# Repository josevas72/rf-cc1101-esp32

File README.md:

# RF CC1101 + ESP32 — placa, firmware ESPHome y caja 3D

Emisor/receptor de radiofrecuencia a **433,92 MHz** con un ESP32 y el módulo **CC1101**
(E07-M1101D), pensado para Home Assistant mediante **ESPHome**. Sirve para controlar por RF
persianas, luces, enchufes o ventiladores con mando, y para escuchar el mando original y mantener
sincronizado el estado.

El repositorio incluye todo lo necesario para reproducirlo: la **placa (PCB)** en KiCad con sus
archivos de fabricación, el **firmware** (plantillas ESPHome) y una **caja imprimible** en 3D.

Hay dos versiones:

- **v2 (recomendada):** placa de **39 × 18 mm** y caja de **48 × 21 × 36,5 mm**. Ver abajo.
- **v1:** la placa original de 58 × 53 mm, con cabecera I2C y caja vertical. Se puede
  descargar tal cual en la etiqueta [`v1.0`](https://github.com/josevas72/rf-cc1101-esp32/releases/tag/v1.0).

## Versión 2: placa pequeña

### Qué cambia respecto a la v1

- Placa de **39,1 × 18,3 mm** (la v1 medía 58,4 × 53,3 mm), 2 capas, 1,6 mm, masa en las dos caras y una sola vía.
- Vista de frente, de izquierda a derecha: **ESP32-C3 SuperMini** en horizontal con el **USB-C por el lateral
  izquierdo**, un **electrolítico de 100 µF** entre 3V3 y GND en medio (pad cuadrado = +) y el zócalo 2×4 del
  **E07-M1101D** con la **antena hacia arriba**.
- Sin GDO2 (emite y recibe por GDO0), sin cabecera I2C y sin los SMD de 10 µF y 100 nF.
- **Los GPIO son los mismos que en la v1**, así que el firmware es prácticamente el mismo.
- Hay otra versión de la misma placa para **XIAO ESP32-C6** (38,1 × 18,3 mm, 2 zócalos 1×7).
  Está diseñada y pasa el DRC, pero **no se ha fabricado todavía**.

| Señal | C3 SuperMini | XIAO ESP32-C6 | E07-M1101D |
|---|---|---|---|
| SCK | GPIO4 | D8 (GPIO19) | 5 |
| MISO | GPIO5 | D9 (GPIO20) | 7 |
| MOSI | GPIO6 | D10 (GPIO18) | 6 |
| CS | GPIO7 | D1 (GPIO1) | 4 |
| GDO0 | GPIO3 | D2 (GPIO2) | 3 |
| 3V3 / GND | 3V3 / GND | 3V3 / GND | 2 / 1 |

### Materiales (v2)

- ESP32-C3 SuperMini y 2 zócalos hembra 1×8 de 2,54 mm.
- Módulo CC1101 **E07-M1101D** (433 MHz) con antena SMA recta (la de las fotos mide 47 mm) y 1 zócalo hembra 2×4.
- Condensador electrolítico de **100 µF** (Ø5 mm, paso 2 mm). Cualquier altura: no tiene nada encima.

### Fabricación

- SuperMini: sube `hardware/pcb-v2/fabricacion/rf_cc1101_v2_D_PCBWay.zip` a PCBWay o JLCPCB
  (2 capas, 1,6 mm, HASL, agujero mínimo 0,4 mm).
- XIAO C6 (sin probar): `rf_cc1101_v2_XIAO_PCBWay.zip`.
- Proyectos KiCad: `hardware/pcb-v2/kicad/` (SuperMini) y `hardware/pcb-v2/kicad-xiao/`. Si lo modificas,
  pulsa **B** para rellenar las zonas de masa antes del DRC.
- `hardware/pcb-v2/generador/generador_placa_v2.py` es el script en Python que generó el diseño
  (`python3 generador_placa_v2.py <carpeta> D` o `X`). Opcional.

### Caja (v2)

`hardware/caja-v2/` contiene el diseño en **OpenSCAD** (paramétrico) y los STL listos para imprimir.

- Exterior **48 × 21 × 36,5 mm** con la tapa. Interior para un conjunto de 43 × 16 × 32 mm con 0,5 mm de holgura.
- La placa va de pie. La **tuerca del SMA aprieta el módulo contra la tapa** y a la vez cierra la caja: no hace falta
  ningún tornillo.
- La tapa abraza la caja por fuera (ajuste 0,05 mm, probado en PLA). Si te queda floja o dura, cambia `ajuste`
  en el `.scad`.
- Hueco del USB-C con rebaje para la funda del cable, ranuras de ventilación, «RF» grabado en el frente y
  huecos para 4 pies de goma.
- La caja se imprime boca arriba y la tapa boca abajo, las dos sin soportes.
- En el `.scad`, `part = "caja" | "tapa" | "ambas" | "montaje"`.

### Firmware (v2)

- **SuperMini:** `firmware/esphome/rf-cc1101-v2-c3-supermini.yaml`. Es la plantilla de la v1 sin I2C,
  con la potencia WiFi a 8,5 dBm y un ejemplo nuevo de **ventilador de techo con 6 velocidades** (entidad
  `fan`). Los códigos de los ejemplos son **falsos**: captura los tuyos con `docs/capturar_codigos_rf.md`.
- **XIAO C6:** sirve `firmware/esphome/rf-cc1101-xiao-c6.yaml` de la v1. Borra el bloque `i2c:` si no
  lo usas.

### Lecciones de la v2

1. La WiFi del SuperMini es floja: cerca de un punto de acceso funciona bien, pero a −80 dBm pierde órdenes.
   Colócalo cerca de un punto de acceso o usa el XIAO.
2. Bajar la potencia WiFi a 8,5 dBm hace que la antena del CC1101 se sature menos.
3. Mide el conjunto montado, con el SMA puesto, antes de diseñar la caja: los planos del módulo no bastan.

---

## Versión 1: placa original

## Fotos

*Arriba: la placa tal como llega de fábrica con los zócalos, el SuperMini y el módulo antes de soldar,
y una primera prueba de encaje. Abajo: la caja impresa con la placa dentro (se ve por las ranuras) y la antena saliendo por la tapa, y las piezas antes de montar.*

## Características

- Placa de 2 capas (58,4 × 53,3 mm) con zócalos para **ESP32-C3 SuperMini** o **XIAO ESP32-C6**
  (se monta uno solo; ver estado de pruebas) y zócalo 2×4 para el módulo **E07-M1101D**.
- Cabecera I2C para un sensor de temperatura (AHT20, BME280, SHT4x…).
- Firmware con el componente nativo `cc1101` de ESPHome, emisión y recepción por un solo pin
  (GDO0) y filtros contra el ruido del receptor.
- **WiFi por portal cautivo**: no hay claves en el código; el dispositivo crea su propia red y
  eliges tu WiFi desde el móvil.
- Caja vertical con peana, tapa tipo caja de zapatos, ventilación, hueco para USB y orificio para
  la antena.

## Estructura del repositorio

```
hardware/
  pcb-v2/             v2: kicad/ (SuperMini), kicad-xiao/, fabricacion/, generador/, img/
  caja-v2/            v2: caja_rf_pequeno.scad, stl/ (caja y tapa), img/
  pcb/                v1:
    kicad/            proyecto KiCad (.kicad_pro, .kicad_pcb, .kicad_sch)
    fabricacion/      ZIP listo para PCBWay/JLCPCB (Gerbers + taladros)
    BOM.csv           lista de materiales
    pcb_rutado.png    vista del rutado
    extras/           script Python que generó el diseño inicial (opcional)
  caja/               v1: caja_rf_cc1101_v4.stl (caja y tapa, listo para imprimir)
firmware/
  esphome/            rf-cc1101-v2-c3-supermini.yaml (v2), rf-cc1101-c3-supermini.yaml y
                      rf-cc1101-xiao-c6.yaml (v1) y secrets.example.yaml
docs/
  capturar_codigos_rf.md   cómo capturar los códigos de un mando
  img/
```

## Hardware

### Conexiones

| Señal | XIAO ESP32-C6 | ESP32-C3 SuperMini |
|---|---|---|
| SCK | GPIO19 (D8) | GPIO4 |
| MISO | GPIO20 (D9) | GPIO5 |
| MOSI | GPIO18 (D10) | GPIO6 |
| CS (CSN) | GPIO1 (D1) | GPIO7 |
| GDO0 | GPIO2 (D2) | GPIO3 |
| GDO2 | GPIO0 (D0) | GPIO10 |
| I2C SDA | GPIO23 (D5) | GPIO0 |
| I2C SCL | GPIO16 (D6) | GPIO1 |

Orden de pines del zócalo del módulo (como el NRF24L01): 1 GND, 2 VCC, 3 GDO0, 4 CSN, 5 SCK,
6 MOSI, 7 MISO, 8 GDO2. El pin 1 lleva el pad cuadrado.

> **Nota XIAO ESP32-C6:** GPIO3 controla el conmutador de antena interno y no sale a ningún pin,
> por eso GDO2 va a GPIO0.

### Lista de materiales

- ESP32-C3 SuperMini **o** XIAO ESP32-C6.
- Módulo CC1101 **E07-M1101D** (433 MHz) con antena SMA.
- Zócalos hembra 2,54 mm: 2 × 1×8 (SuperMini) o 2 × 1×7 (XIAO) y 1 × 2×4.
- Cabecera macho 1×4 para el sensor I2C.
- Condensadores 0805: 10 µF (C1) y 100 nF (C2). Recomendable además un electrolítico de
  100 µF entre 3V3 y GND.
- 2 tornillos M2 × 4 mm autorroscantes (tapa de la caja).

### Fabricación de la PCB

1. Abre `hardware/pcb/kicad/rf_cc1101.kicad_pro` con KiCad 8 o superior.
2. Pulsa **B** para rellenar las zonas de masa y ejecuta el DRC.
3. Para pedirla, sube `hardware/pcb/fabricacion/rf_cc1101_PCBWay.zip` (9 Gerbers y el archivo de
   taladros `.txt`) a tu fabricante. Opciones: 2 capas, 1,6 mm, HASL.

Estado de las pruebas:

- **ESP32-C3 SuperMini:** probado en la PCB, funcionando en producción.
- **XIAO ESP32-C6:** probado y funcionando en producción en un prototipo **cableado a mano**.
  En esta PCB se ha verificado la continuidad de todos los GPIO entre el ESP32-C6 y el CC1101,
  pero **la PCB aún no se ha montado con el XIAO**.

## Firmware (ESPHome)

Necesita **ESPHome 2026.9 o superior**.

1. Elige el archivo de tu placa: `rf-cc1101-c3-supermini.yaml` o `rf-cc1101-xiao-c6.yaml`
   (solo cambian los pines y la placa) y cópialo a tu carpeta de ESPHome.
2. Rellena la sección `substitutions:` del principio (nombre, nombre amistoso, red y **contraseña
   del punto de acceso**). Opcionalmente genera una clave para la API. Compila y graba por USB:
   `esphome run rf-cc1101-c3-supermini.yaml`.
3. Conéctate a la red **RF-CC1101 Config** (se abre el portal; si no, entra en
   `http://192.168.33.1`), elige tu WiFi e introduce la clave.
4. Home Assistant detectará el dispositivo. Si más adelante cambia el router, la red de
   configuración reaparece sola; también puedes mantener 10 s el botón BOOT para restablecer el
   WiFi.

Decisiones de configuración que funcionan bien:

- Pin único GDO0 para emitir y recibir con `cc1101.set_idle` / `begin_tx` / `begin_rx`.
- `filter_bandwidth: 100kHz` y `filter: 150us` en el receptor contra el ruido. Si hay ruido, prueba
  `rx_attenuation`.
- `output_power: 10dBm` en el WiFi del SuperMini para mantener la conexión estable.
- Usar GDO2 como pin de recepción separado recibía bien pero no permitía emitir; se descartó.

Al final de cada YAML hay ejemplos comentados de **persiana** y **ventilador/luz** con `xxxxx` en
lugar de códigos: son los que capturas con tu mando siguiendo `docs/capturar_codigos_rf.md`
(incluye captura de códigos raw y cómo adaptar el protocolo con ayuda de Claude).

## Caja 3D

`hardware/caja/caja_rf_cc1101_v4.stl` incluye caja y tapa, listas para imprimir (158,2 × 54,6 × 83,5 mm):

- Interior útil 54 × 25 × 80 mm, con peana ancha para que no vuelque.
- Placa de pie, antena hacia arriba por la tapa (Ø7 mm) y USB lateral.
- Ventilación por ranuras, nervio y pestañas que retienen la placa.
- Tapa que abraza el labio de la caja, fijada con 2 tornillos M2 × 4 mm laterales.

## Lecciones aprendidas

1. El ruido del receptor con antena puede saturar al ESP32 y tirar el WiFi: se resuelve con los
   filtros del CC1101 y del receptor.
2. En el XIAO ESP32-C6 no se puede usar GPIO3.
3. Los tacos de los tornillos de la tapa deben sobresalir poco para que la placa entre por arriba.

## Licencia

MIT (ver `LICENSE`). Si prefieres una licencia de hardware abierto para la PCB y la caja, por
ejemplo CERN-OHL-P o CC BY-SA 4.0, cámbiala antes de publicar.

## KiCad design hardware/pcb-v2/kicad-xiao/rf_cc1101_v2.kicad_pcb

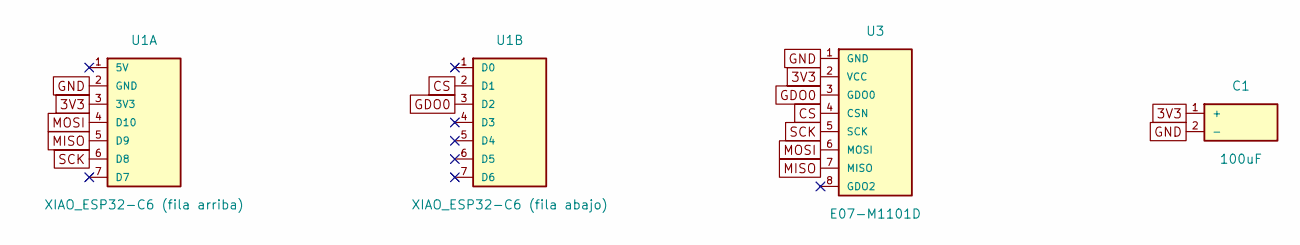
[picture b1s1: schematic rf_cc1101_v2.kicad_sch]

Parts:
C1: 100uF; CP_Radial_D5.0mm_P2.00mm
U1A: XIAO_ESP32-C6 (fila arriba); PinSocket_1x07_P2.54mm_Vertical
U1B: XIAO_ESP32-C6 (fila abajo); PinSocket_1x07_P2.54mm_Vertical
U3: E07-M1101D; PinSocket_2x04_P2.54mm_Vertical

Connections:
3V3: C1.1 (+), U1A.3 (3V3), U3.2 (VCC)
CS: U1B.2 (D1), U3.4 (CSN)
GDO0: U1B.3 (D2), U3.3 (GDO0)
GND: C1.2 (-), U1A.2 (GND), U3.1 (GND)
MISO: U1A.5 (D9), U3.7 (MISO)
MOSI: U1A.4 (D10), U3.6 (MOSI)
SCK: U1A.6 (D8), U3.5 (SCK)

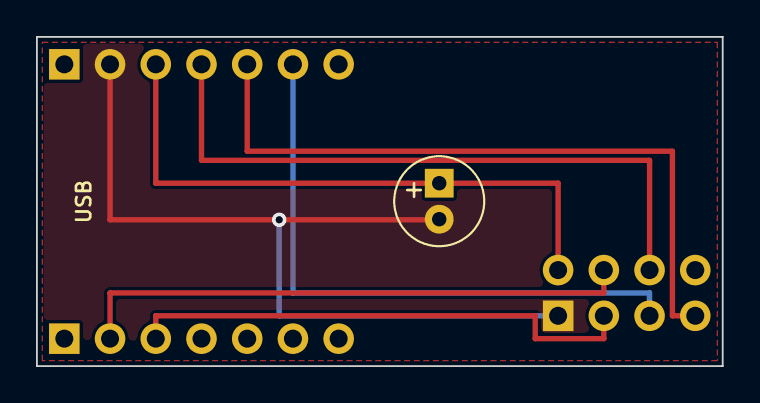
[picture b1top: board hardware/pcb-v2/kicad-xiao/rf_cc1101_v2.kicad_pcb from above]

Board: 2 copper layers, 38.1 x 18.3 mm, 4 parts (0 on the bottom side), 7 nets.

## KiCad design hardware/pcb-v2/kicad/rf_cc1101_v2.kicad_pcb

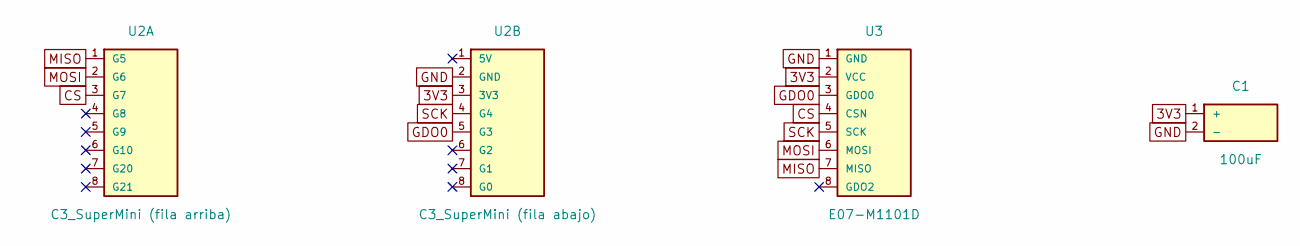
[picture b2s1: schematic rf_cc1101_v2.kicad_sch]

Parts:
C1: 100uF; CP_Radial_D5.0mm_P2.00mm
U2A: C3_SuperMini (fila arriba); PinSocket_1x08_P2.54mm_Vertical
U2B: C3_SuperMini (fila abajo); PinSocket_1x08_P2.54mm_Vertical
U3: E07-M1101D; PinSocket_2x04_P2.54mm_Vertical

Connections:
3V3: C1.1 (+), U2B.3 (3V3), U3.2 (VCC)
CS: U2A.3 (G7), U3.4 (CSN)
GDO0: U2B.5 (G3), U3.3 (GDO0)
GND: C1.2 (-), U2B.2 (GND), U3.1 (GND)
MISO: U2A.1 (G5), U3.7 (MISO)
MOSI: U2A.2 (G6), U3.6 (MOSI)
SCK: U2B.4 (G4), U3.5 (SCK)

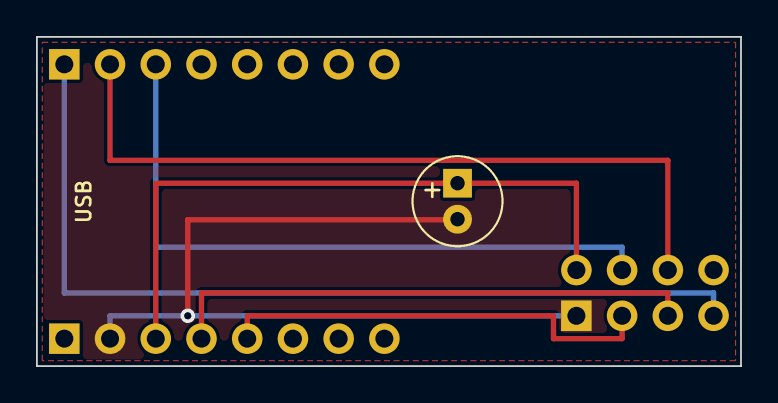
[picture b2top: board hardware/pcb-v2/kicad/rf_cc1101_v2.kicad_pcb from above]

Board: 2 copper layers, 39.1 x 18.3 mm, 4 parts (0 on the bottom side), 7 nets.

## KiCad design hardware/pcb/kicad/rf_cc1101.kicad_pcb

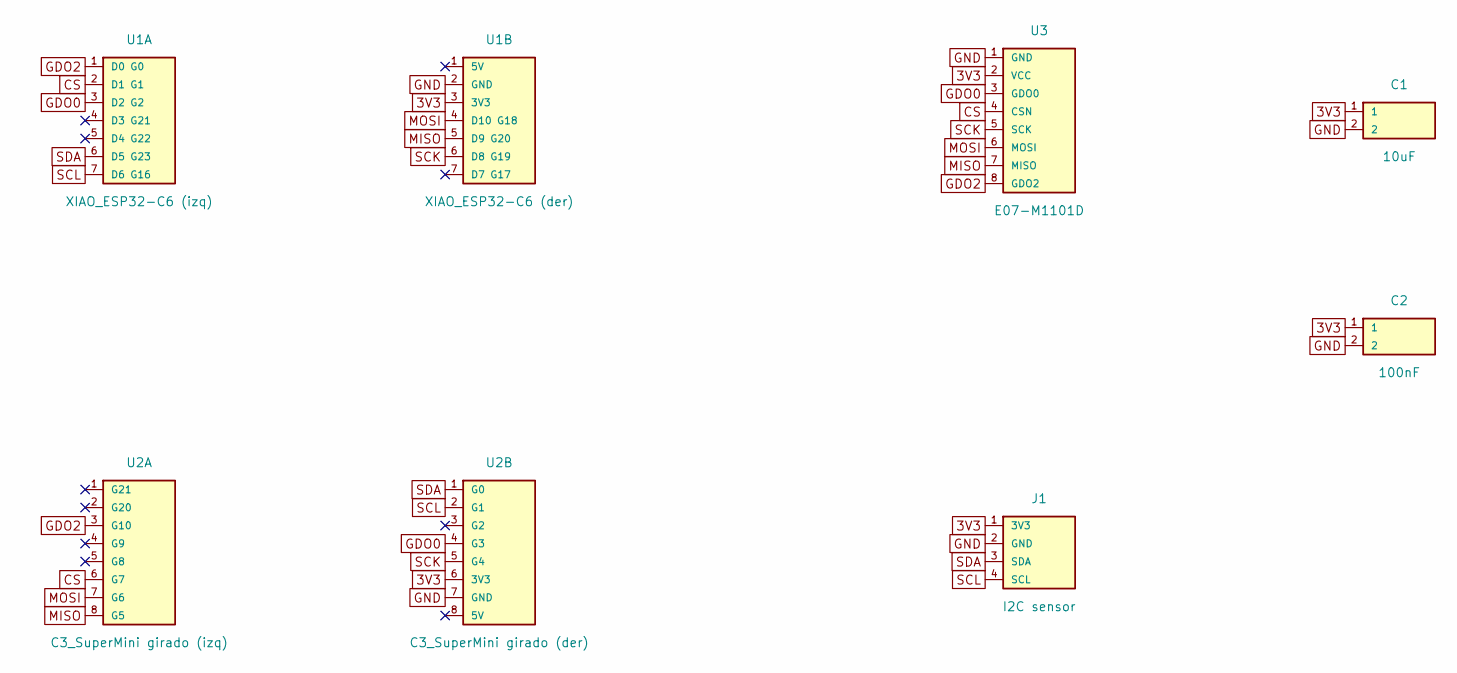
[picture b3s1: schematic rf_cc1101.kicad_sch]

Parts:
C1: 10uF; C_0805_2012Metric
C2: 100nF; C_0805_2012Metric
J1: I2C sensor; PinHeader_1x04_P2.54mm_Vertical
U1A: XIAO_ESP32-C6 (izq); PinSocket_1x07_P2.54mm_Vertical
U1B: XIAO_ESP32-C6 (der); PinSocket_1x07_P2.54mm_Vertical
U2A: C3_SuperMini girado (izq); PinSocket_1x08_P2.54mm_Vertical
U2B: C3_SuperMini girado (der); PinSocket_1x08_P2.54mm_Vertical
U3: E07-M1101D; PinSocket_2x04_P2.54mm_Vertical

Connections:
3V3: C1.1, C2.1, J1.1 (3V3), U1B.3 (3V3), U2B.6 (3V3), U3.2 (VCC)
CS: U1A.2 (D1 G1), U2A.6 (G7), U3.4 (CSN)
GDO0: U1A.3 (D2 G2), U2B.4 (G3), U3.3 (GDO0)
GDO2: U1A.1 (D0 G0), U2A.3 (G10), U3.8 (GDO2)
GND: C1.2, C2.2, J1.2 (GND), U1B.2 (GND), U2B.7 (GND), U3.1 (GND)
MISO: U1B.5 (D9 G20), U2A.8 (G5), U3.7 (MISO)
MOSI: U1B.4 (D10 G18), U2A.7 (G6), U3.6 (MOSI)
SCK: U1B.6 (D8 G19), U2B.5 (G4), U3.5 (SCK)
SCL: J1.4 (SCL), U1A.7 (D6 G16), U2B.2 (G1)
SDA: J1.3 (SDA), U1A.6 (D5 G23), U2B.1 (G0)

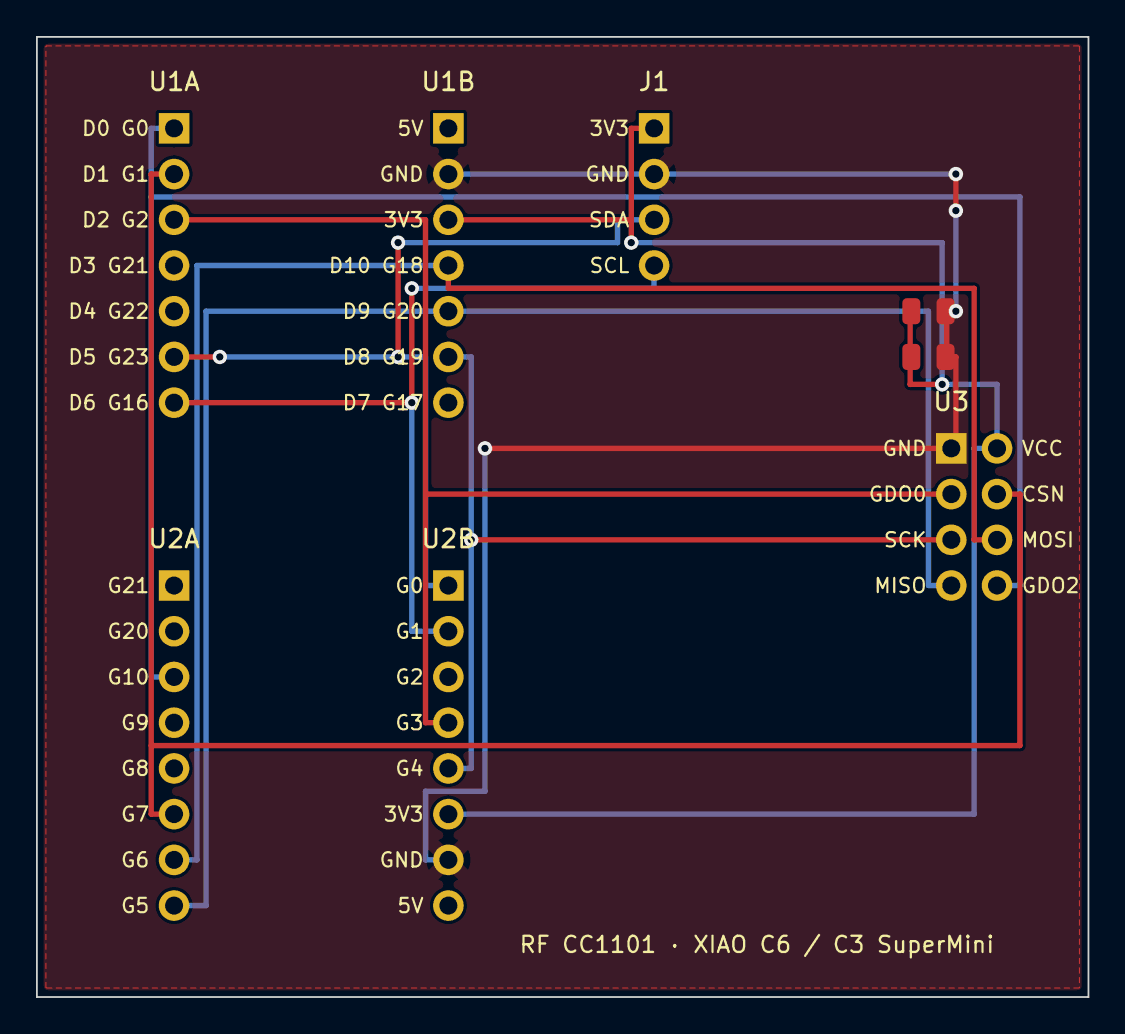
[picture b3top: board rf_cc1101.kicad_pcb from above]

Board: 2 copper layers, 58.4 x 53.3 mm, 8 parts (0 on the bottom side), 10 nets.
